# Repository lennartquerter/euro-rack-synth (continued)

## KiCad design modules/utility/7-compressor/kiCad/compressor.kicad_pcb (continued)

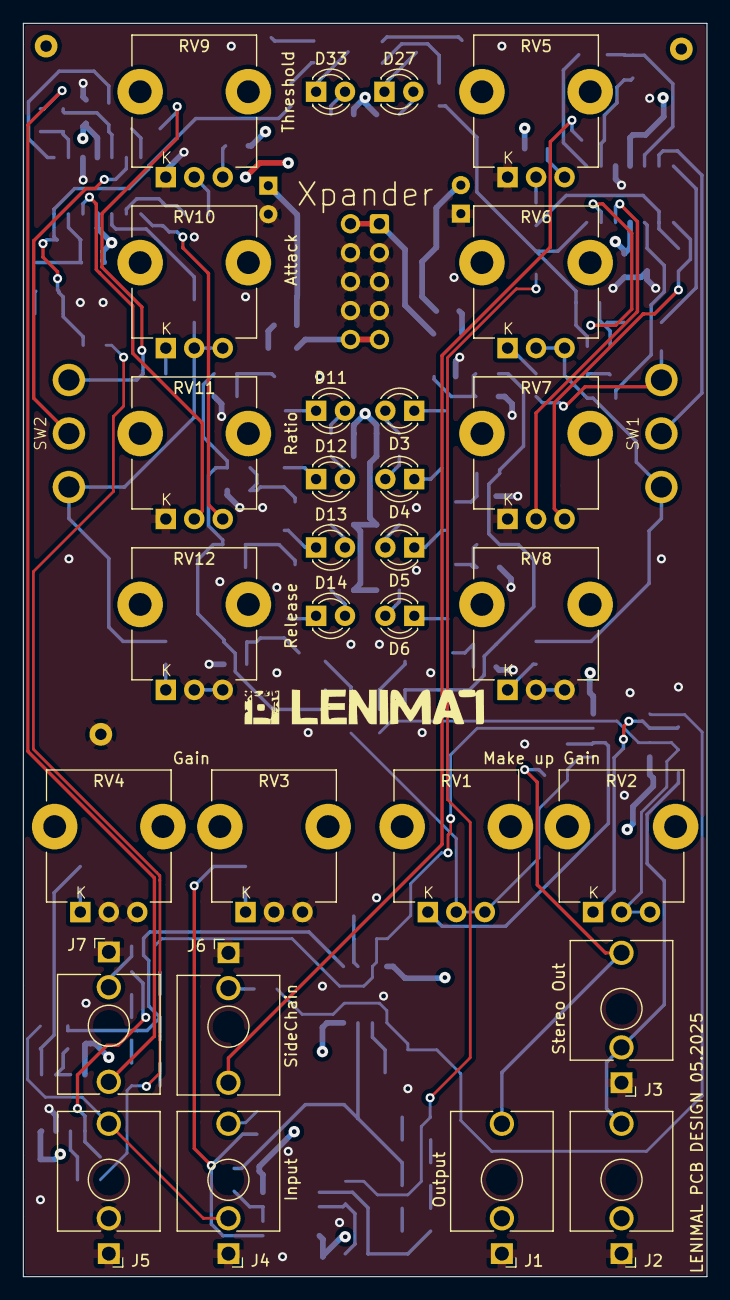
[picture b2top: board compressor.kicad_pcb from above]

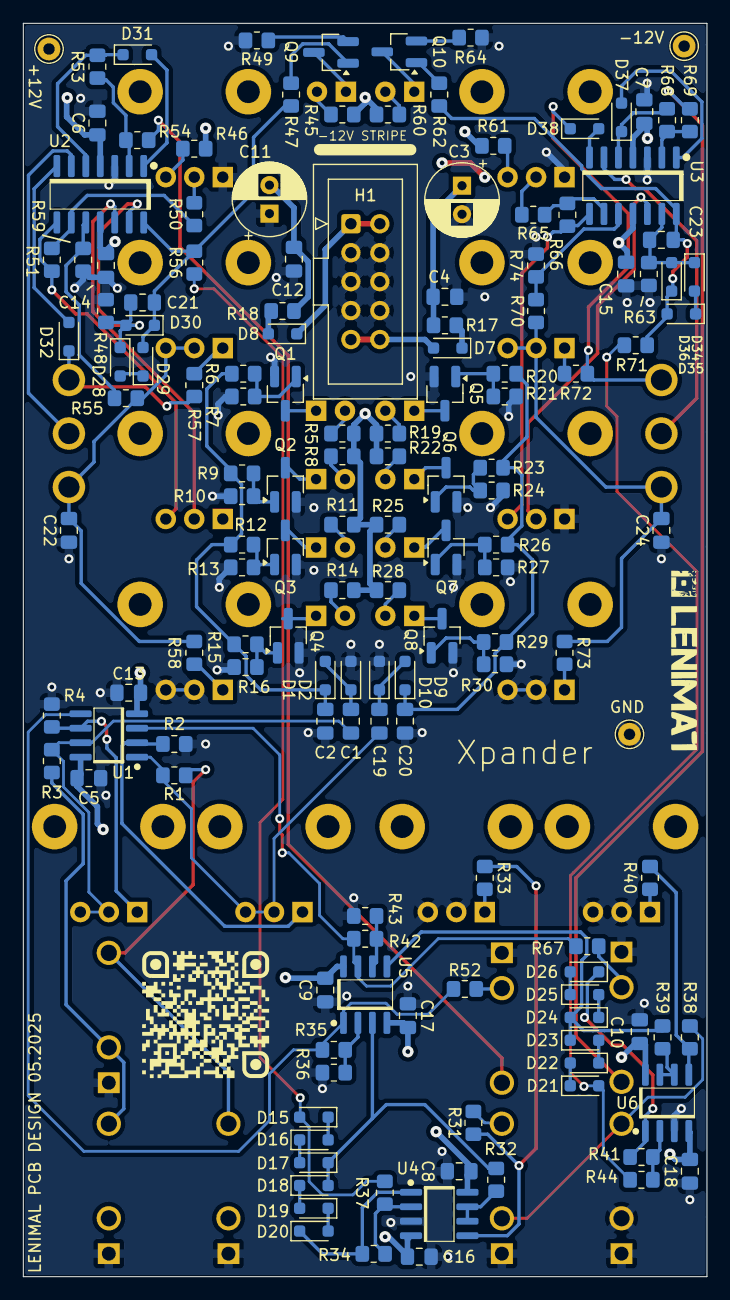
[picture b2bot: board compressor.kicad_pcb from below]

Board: 4 copper layers, 60.0 x 110.0 mm, 177 parts (146 on the bottom side), 117 nets.

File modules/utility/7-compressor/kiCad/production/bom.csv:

Designator,Footprint,Quantity,Value,LCSC Part #
"C1, C19, C2, C20, C22, C24",0805,6,1.5uF,
"C10, C12, C13, C14, C15, C16, C17, C18, C4, C5, C6, C7, C8, C9",0805,14,100nF,
"C11, C3",CP_Radial_D6.3mm_P2.50mm,2,47uF,
"C21, C23",0805,2,680pF,
"D1, D10, D15, D16, D17, D18, D19, D2, D20, D21, D22, D23, D24, D25, D26, D28, D29, D30, D31, D32, D34, D35, D36, D37, D38, D9",D_SOD-323_HandSoldering,26,1N4148WS,
"D11, D12, D13, D14, D27, D3, D33, D4, D5, D6",LED_D3.0mm,10,LED,
"D7, D8",D_SOD-323_HandSoldering,2,1N5819WS,
H1,IDC-Header_2x05_P2.54mm_Vertical,1,Conn_02x05_PWR_Eurorack,
J1,Jack_3.5mm_QingPu_WQP-PJ398SM_Vertical_CircularHoles,1,LEFT_OUT,
J2,Jack_3.5mm_QingPu_WQP-PJ398SM_Vertical_CircularHoles,1,RIGHT_OUT,
J3,Jack_3.5mm_QingPu_WQP-PJ398SM_Vertical_CircularHoles,1,STEREO_OUT,
"J4, J5",Jack_3.5mm_QingPu_WQP-PJ398SM_Vertical_CircularHoles,2,INPUT,
"J6, J7",Jack_3.5mm_QingPu_WQP-PJ398SM_Vertical_CircularHoles,2,SIDECHAIN_IN,
"Q1, Q10, Q2, Q3, Q4, Q5, Q6, Q7, Q8, Q9",SOT-23_Handsoldering,10,MMBT3904,
"R1, R3, R52, R67",0805,4,1K,
"R10, R13, R16, R21, R24, R27, R30, R7",0805,8,33K,
"R11, R14, R19, R22, R25, R28, R5, R8",0805,8,3K3,
"R12, R26",0805,2,220K,
"R15, R29",0805,2,330K,
"R17, R18",0805,2,10R,
"R2, R4",0805,2,20K,
"R20, R6",0805,2,47K,
"R23, R9",0805,2,120K,
"R31, R32, R34, R35, R37, R38, R39, R41, R42, R44, R48, R50, R51, R53, R54, R58, R63, R65, R66, R68, R69, R73",0805,22,100K,
"R33, R36, R40, R43, R46, R47, R61, R62",0805,8,10K,
"R45, R60",0805,2,470R,
"R49, R64",0805,2,0R,
"R55, R59, R70, R74",0805,4,470K,
"R56, R71",0805,2,2K,
"R57, R72",0805,2,200R,
"RV1, RV11, RV2, RV7",Potentiometer_TT_P0915N,4,A100K,
"RV10, RV6",Potentiometer_TT_P0915N,2,A500K,
"RV12, RV8",Potentiometer_TT_P0915N,2,A1M,
"RV3, RV4",Potentiometer_TT_P0915N,2,A20K,
"RV5, RV9",Potentiometer_TT_P0915N,2,A10K,
"SW1, SW2",SW_default,2,SW_SPDT,
"U1, U4, U5, U6",SOIC-8,4,TL072,
"U2, U3",SOIC-14,2,TL074,

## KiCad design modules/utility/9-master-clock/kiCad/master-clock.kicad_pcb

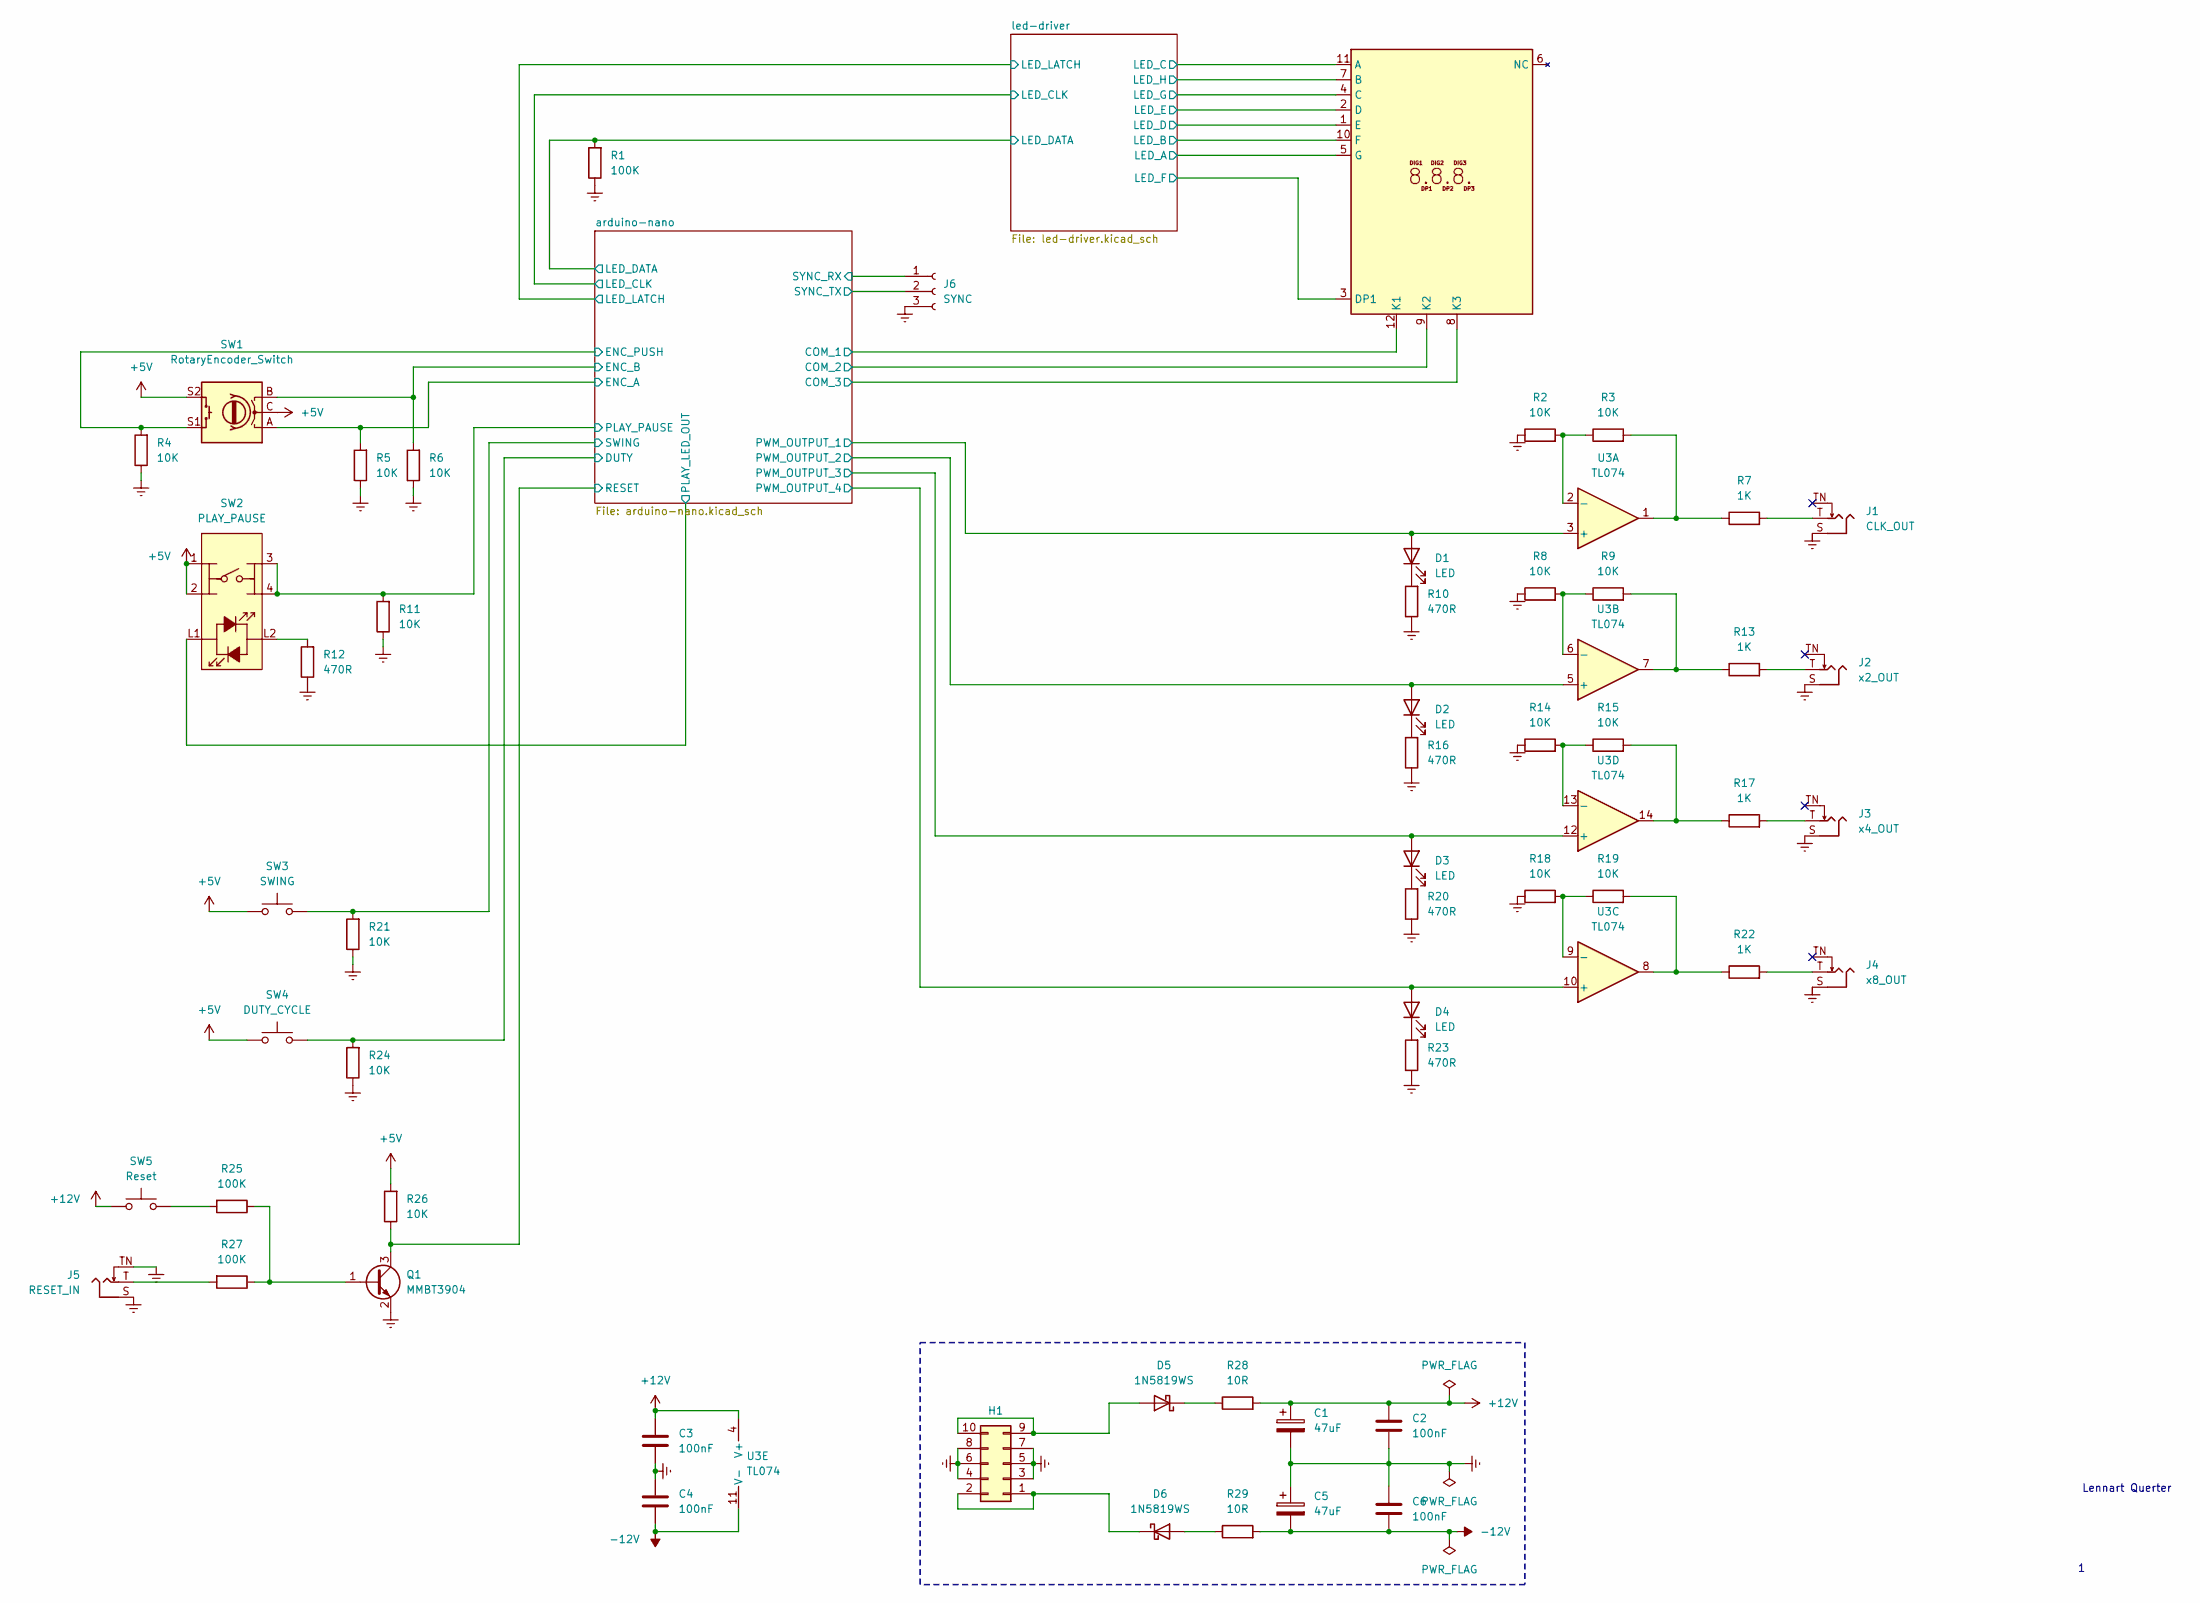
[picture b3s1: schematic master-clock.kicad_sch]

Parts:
C1, C5: 47uF; CP_Radial_D5.0mm_P2.50mm
C2, C3, C4, C6: 100nF; C_0805_2012Metric_Pad1.18x1.45mm_HandSolder
D1, D2, D3, D4: LED; LED_D3.0mm
D5, D6: 1N5819WS; D_SOD-323_HandSoldering
H1: Conn_02x05_PWR_Eurorack; PinSocket_2x05_P2.54mm_Vertical
J1: CLK_OUT; Jack_3.5mm_QingPu_WQP-PJ398SM_Vertical_CircularHoles
J2: x2_OUT; Jack_3.5mm_QingPu_WQP-PJ398SM_Vertical_CircularHoles
J3: x4_OUT; Jack_3.5mm_QingPu_WQP-PJ398SM_Vertical_CircularHoles
J4: x8_OUT; Jack_3.5mm_QingPu_WQP-PJ398SM_Vertical_CircularHoles
J5: RESET_IN; Jack_3.5mm_QingPu_WQP-PJ398SM_Vertical_CircularHoles
J6: SYNC; PinSocket_1x03_P2.54mm_Vertical
Q1: MMBT3904; SOT-23_Handsoldering
R1, R25, R27: 100K; R_0805_2012Metric_Pad1.20x1.40mm_HandSolder
R2, R3, R4, R5, R6, R8, R9, R11, R14, R15, R18, R19, R21, R24, R26: 10K; R_0805_2012Metric_Pad1.20x1.40mm_HandSolder
R7, R13, R17, R22: 1K; R_0805_2012Metric_Pad1.20x1.40mm_HandSolder
R10, R12, R16, R20, R23: 470R; R_0805_2012Metric_Pad1.20x1.40mm_HandSolder
R28, R29: 10R; R_0805_2012Metric_Pad1.20x1.40mm_HandSolder
SW1: RotaryEncoder_Switch; RotaryEncoder_Alps_EC11E-Switch_Vertical_H20mm_CircularMoun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
SW2: PLAY_PAUSE; ML6-H2T2GQA
SW3: SWING; SW_PUSH_6mm
SW4: DUTY_CYCLE; SW_PUSH_6mm
SW5: Reset; SW_PUSH_6mm
U1: 3x7-segment_display; 3x7-segment-display_SP410361N
U3: TL074; SOIC-14

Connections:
+5V: R26.2, SW1.C, SW1.S2, SW2.1, SW2.2, SW3.1, SW4.1; also elsewhere on the board
+12V: C1.1, C2.1, C3.1, R28.2, SW5.1, U3.4 (V+); also elsewhere on the board
-12V: C4.2, C5.2, C6.2, R29.2, U3.11 (V-)
/arduino-nano/COM_1: U1.12 (K1); also elsewhere on the board
/arduino-nano/COM_2: U1.9 (K2); also elsewhere on the board
/arduino-nano/COM_3: U1.8 (K3); also elsewhere on the board
/arduino-nano/DUTY: R24.2, SW4.2; also elsewhere on the board
/arduino-nano/ENC_A: R5.2, SW1.A; also elsewhere on the board
/arduino-nano/ENC_B: R6.2, SW1.B; also elsewhere on the board
/arduino-nano/ENC_PUSH: R4.2, SW1.S1; also elsewhere on the board
/arduino-nano/LED_DATA: R1.2; also elsewhere on the board
/arduino-nano/PLAY_LED_OUT: SW2.L1; also elsewhere on the board
/arduino-nano/PLAY_PAUSE: R11.2, SW2.3, SW2.4 (A); also elsewhere on the board
/arduino-nano/PWM_OUTPUT_1: D1.2 (A), U3.3 (+); also elsewhere on the board
/arduino-nano/PWM_OUTPUT_2: D2.2 (A), U3.5 (+); also elsewhere on the board
/arduino-nano/PWM_OUTPUT_3: D3.2 (A), U3.12 (+); also elsewhere on the board
/arduino-nano/PWM_OUTPUT_4: D4.2 (A), U3.10 (+); also elsewhere on the board
/arduino-nano/RESET: Q1.3 (C), R26.1; also elsewhere on the board
/arduino-nano/SWING: R21.2, SW3.2; also elsewhere on the board
/arduino-nano/SYNC_RX: J6.1; also elsewhere on the board
/arduino-nano/SYNC_TX: J6.2; also elsewhere on the board
/led-driver/LED_A: U1.5 (G); also elsewhere on the board
/led-driver/LED_B: U1.10 (F); also elsewhere on the board
/led-driver/LED_C: U1.11 (A); also elsewhere on the board
/led-driver/LED_D: U1.1 (E); also elsewhere on the board
/led-driver/LED_E: U1.2 (D); also elsewhere on the board
/led-driver/LED_F: U1.3 (DP1); also elsewhere on the board
/led-driver/LED_G: U1.4 (C); also elsewhere on the board
/led-driver/LED_H: U1.7 (B); also elsewhere on the board
GNDREF: C1.2, C2.2, C3.2, C4.1, C5.1, C6.1, H1.3, H1.4, H1.5, H1.6, H1.7, H1.8, J1.S, J2.S, J3.S, J4.S, J5.S, J5.TN, J6.3, Q1.2 (E), R1.1, R2.1, R4.1, R5.1, R6.1, R8.1, R10.1, R11.1, R12.1, R14.1, R16.1, R18.1, R20.1, R21.1, R23.1, R24.1; also elsewhere on the board
unnamed: D1.1 (K), R10.2
unnamed: D2.1 (K), R16.2
unnamed: D3.1 (K), R20.2
unnamed: D4.1 (K), R23.2
unnamed: D5.2 (A), H1.9, H1.10
unnamed: D5.1 (K), R28.1
unnamed: D6.2 (A), R29.1
unnamed: D6.1 (K), H1.1, H1.2
unnamed: J1.T, R7.2
unnamed: J2.T, R13.2
unnamed: J3.T, R17.2
unnamed: J4.T, R22.2
unnamed: J5.T, R27.2
unnamed: Q1.1 (B), R25.1, R27.1
unnamed: R3.2, R7.1, U3.1
unnamed: R12.2, SW2.L2
unnamed: R9.2, R13.1, U3.7
unnamed: R15.2, R17.1, U3.14
unnamed: R19.2, R22.1, U3.8
unnamed: R25.2, SW5.2
unnamed: R2.2, R3.1, U3.2 (-)
unnamed: R8.2, R9.1, U3.6 (-)
unnamed: R18.2, R19.1, U3.9 (-)
unnamed: R14.2, R15.1, U3.13 (-)

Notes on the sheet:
Lennart Querter

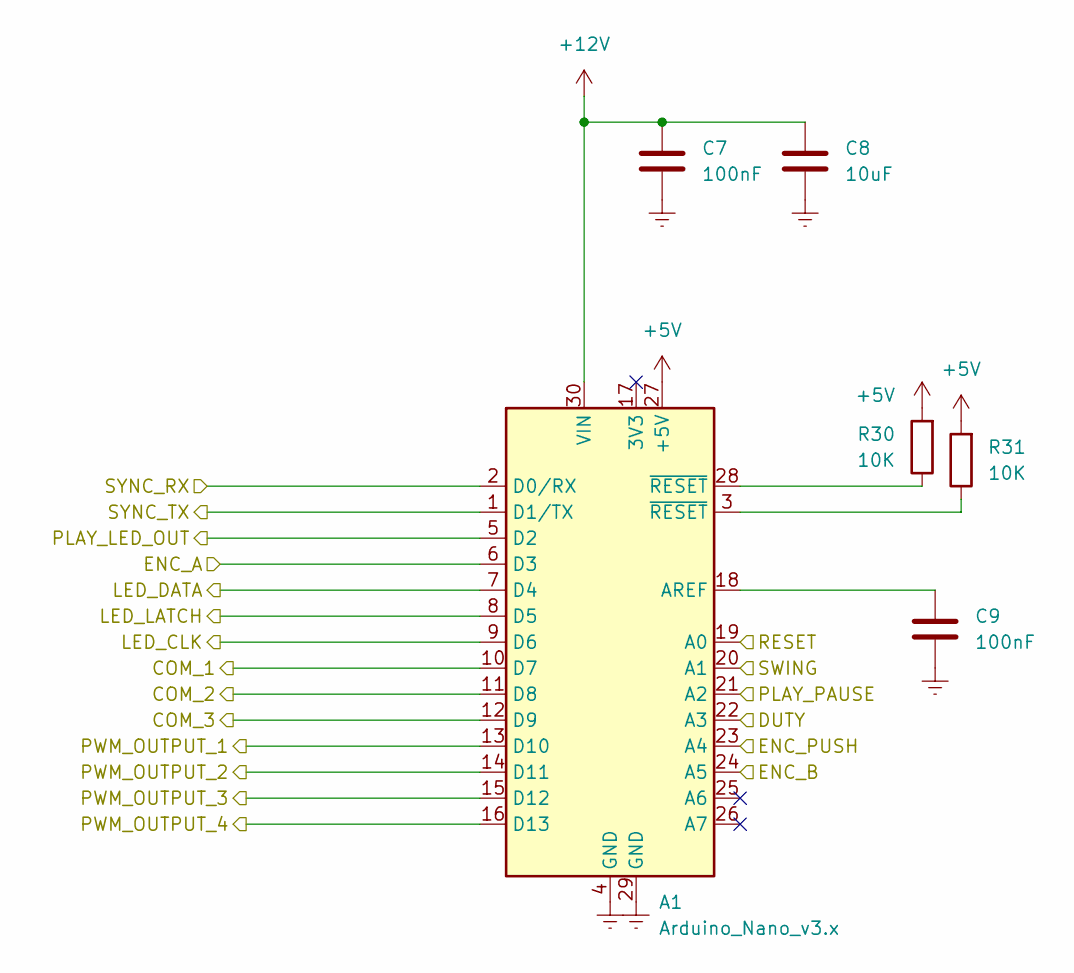
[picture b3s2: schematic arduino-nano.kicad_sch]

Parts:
A1: Arduino_Nano_v3.x; Arduino_Nano_MOD
C7, C9: 100nF; C_0805_2012Metric_Pad1.18x1.45mm_HandSolder
C8: 10uF; C_0805_2012Metric_Pad1.18x1.45mm_HandSolder
R30, R31: 10K; R_0805_2012Metric_Pad1.20x1.40mm_HandSolder

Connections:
+5V: A1.27 (+5V), R30.2, R31.2; also elsewhere on the board
+12V: A1.30 (VIN), C7.1, C8.1; also elsewhere on the board
/arduino-nano/COM_1: A1.10 (D7); also elsewhere on the board
/arduino-nano/COM_2: A1.11 (D8); also elsewhere on the board
/arduino-nano/COM_3: A1.12 (D9); also elsewhere on the board
/arduino-nano/DUTY: A1.22 (A3); also elsewhere on the board
/arduino-nano/ENC_A: A1.6 (D3); also elsewhere on the board
/arduino-nano/ENC_B: A1.24 (A5); also elsewhere on the board
/arduino-nano/ENC_PUSH: A1.23 (A4); also elsewhere on the board
/arduino-nano/LED_CLK: A1.9 (D6); also elsewhere on the board
/arduino-nano/LED_DATA: A1.7 (D4); also elsewhere on the board
/arduino-nano/LED_LATCH: A1.8 (D5); also elsewhere on the board
/arduino-nano/PLAY_LED_OUT: A1.5 (D2); also elsewhere on the board
/arduino-nano/PLAY_PAUSE: A1.21 (A2); also elsewhere on the board
/arduino-nano/PWM_OUTPUT_1: A1.13 (D10); also elsewhere on the board
/arduino-nano/PWM_OUTPUT_2: A1.14 (D11); also elsewhere on the board
/arduino-nano/PWM_OUTPUT_3: A1.15 (D12); also elsewhere on the board
/arduino-nano/PWM_OUTPUT_4: A1.16 (D13); also elsewhere on the board
/arduino-nano/RESET: A1.19 (A0); also elsewhere on the board
/arduino-nano/SWING: A1.20 (A1); also elsewhere on the board
/arduino-nano/SYNC_RX: A1.2 (D0/RX); also elsewhere on the board
/arduino-nano/SYNC_TX: A1.1 (D1/TX); also elsewhere on the board
GNDREF: A1.4 (GND), A1.29 (GND), C7.2, C8.2, C9.2; also elsewhere on the board
unnamed: A1.18 (AREF), C9.1
unnamed: A1.3 (~RESET), R31.1
unnamed: A1.28 (~RESET), R30.1

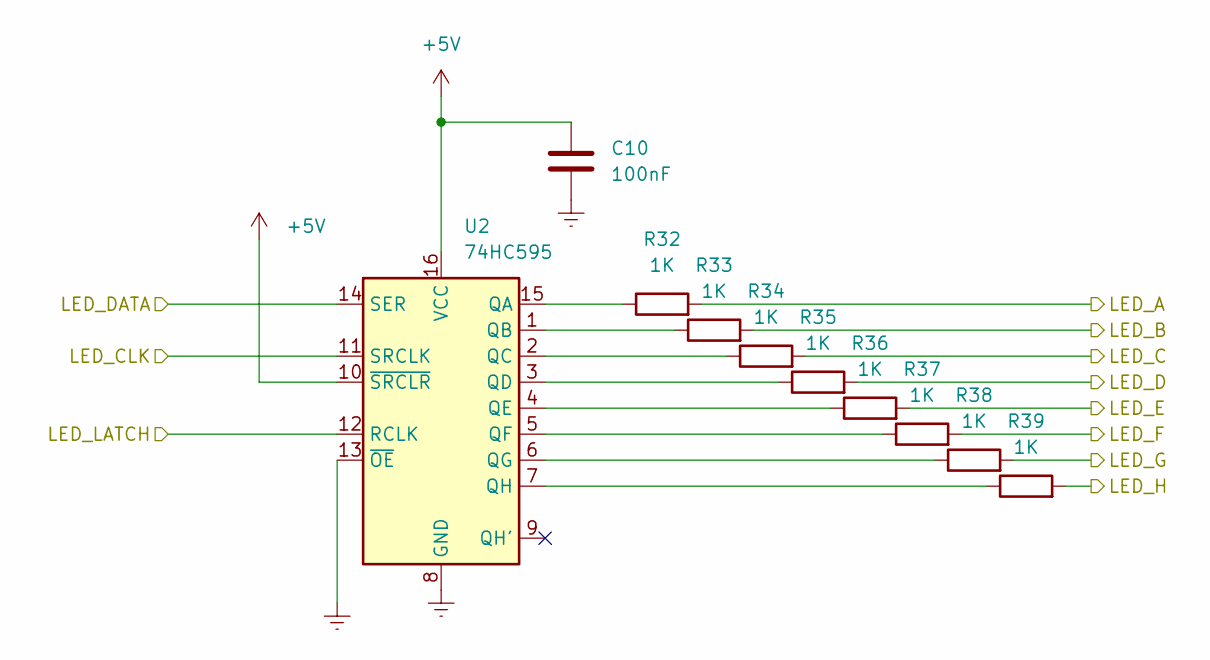
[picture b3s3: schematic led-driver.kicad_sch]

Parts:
C10: 100nF; C_0805_2012Metric_Pad1.18x1.45mm_HandSolder
R32, R33, R34, R35, R36, R37, R38, R39: 1K; R_0805_2012Metric_Pad1.20x1.40mm_HandSolder
U2: 74HC595; SOIC-16

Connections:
+5V: C10.1, U2.10 (~SRCLR), U2.16 (VCC); also elsewhere on the board
/arduino-nano/LED_CLK: U2.11 (SRCLK); also elsewhere on the board
/arduino-nano/LED_DATA: U2.14 (SER); also elsewhere on the board
/arduino-nano/LED_LATCH: U2.12 (RCLK); also elsewhere on the board
/led-driver/LED_A: R32.2; also elsewhere on the board
/led-driver/LED_B: R33.2; also elsewhere on the board
/led-driver/LED_C: R34.2; also elsewhere on the board
/led-driver/LED_D: R35.2; also elsewhere on the board
/led-driver/LED_E: R36.2; also elsewhere on the board
/led-driver/LED_F: R37.2; also elsewhere on the board
/led-driver/LED_G: R38.2; also elsewhere on the board
/led-driver/LED_H: R39.2; also elsewhere on the board
GNDREF: C10.2, U2.8 (GND), U2.13 (~OE); also elsewhere on the board
unnamed: R32.1, U2.15 (QA)
unnamed: R33.1, U2.1 (QB)
unnamed: R34.1, U2.2 (QC)
unnamed: R35.1, U2.3 (QD)
unnamed: R36.1, U2.4 (QE)
unnamed: R37.1, U2.5 (QF)
unnamed: R38.1, U2.6 (QG)
unnamed: R39.1, U2.7 (QH)

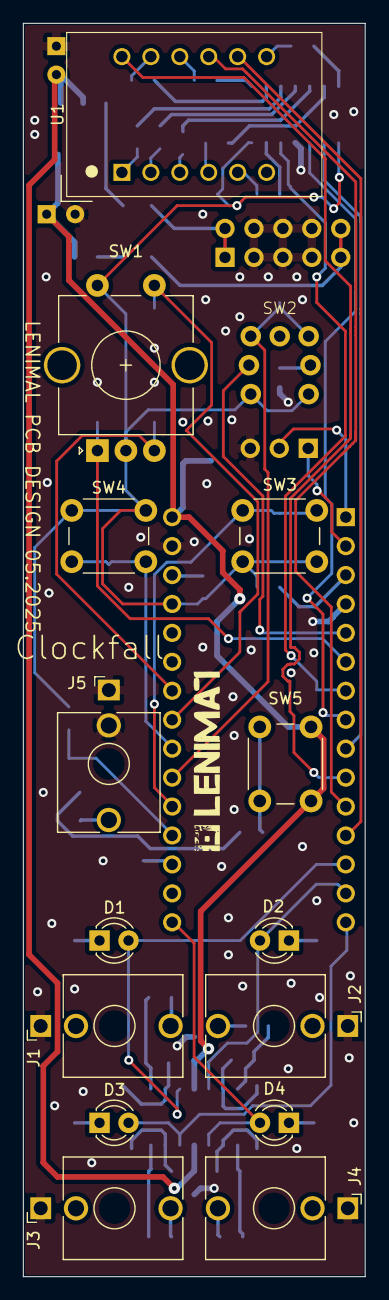
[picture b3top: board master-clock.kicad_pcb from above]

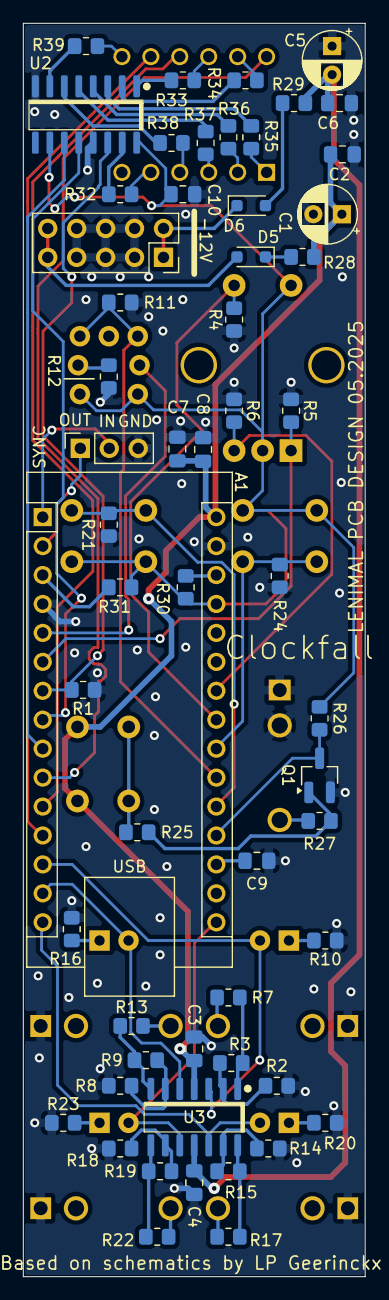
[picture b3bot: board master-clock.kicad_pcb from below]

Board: 2 copper layers, 30.0 x 110.0 mm, 72 parts (57 on the bottom side), 67 nets.

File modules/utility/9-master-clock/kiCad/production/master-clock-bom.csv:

Designator,Footprint,Quantity,Value,LCSC Part #
A1,Arduino_Nano_MOD,1,Arduino_Nano_v3.x,
"C1, C5",CP_Radial_D5.0mm_P2.50mm,2,47uF,
"C10, C2, C3, C4, C6, C7, C9",0805,7,100nF,
C8,0805,1,10uF,
"D1, D2, D3, D4",LED_D3.0mm,4,LED,
"D5, D6",D_SOD-323_HandSoldering,2,1N5819WS,
H1,PinSocket_2x05_P2.54mm_Vertical,1,Conn_02x05_PWR_Eurorack,
J1,Jack_3.5mm_QingPu_WQP-PJ398SM_Vertical_CircularHoles,1,CLK_OUT,
J2,Jack_3.5mm_QingPu_WQP-PJ398SM_Vertical_CircularHoles,1,x2_OUT,
J3,Jack_3.5mm_QingPu_WQP-PJ398SM_Vertical_CircularHoles,1,x4_OUT,
J4,Jack_3.5mm_QingPu_WQP-PJ398SM_Vertical_CircularHoles,1,x8_OUT,
J5,Jack_3.5mm_QingPu_WQP-PJ398SM_Vertical_CircularHoles,1,RESET_IN,
J6,PinSocket_1x03_P2.54mm_Vertical,1,SYNC,
Q1,SOT-23_Handsoldering,1,MMBT3904,
"R1, R25, R27",0805,3,100K,
"R10, R12, R16, R20, R23",0805,5,470R,
"R11, R14, R15, R18, R19, R2, R21, R24, R26, R3, R30, R31, R4, R5, R6, R8, R9",0805,17,10K,
"R13, R17, R22, R32, R33, R34, R35, R36, R37, R38, R39, R7",0805,12,1K,
"R28, R29",0805,2,10R,
SW1,RotaryEncoder_Alps_EC11E-Switch_Vertical_H20mm_CircularMountingHoles,1,RotaryEncoder_Switch,
SW2,ML6-H2T2GQA,1,PLAY_PAUSE,
SW3,SW_PUSH_6mm,1,SWING,
SW4,SW_PUSH_6mm,1,DUTY_CYCLE,
SW5,SW_PUSH_6mm,1,Reset,
U1,3x7-segment-display_SP410361N,1,3x7-segment_display,
U2,SOIC-16,1,74HC595,
U3,SOIC-14,1,TL074,

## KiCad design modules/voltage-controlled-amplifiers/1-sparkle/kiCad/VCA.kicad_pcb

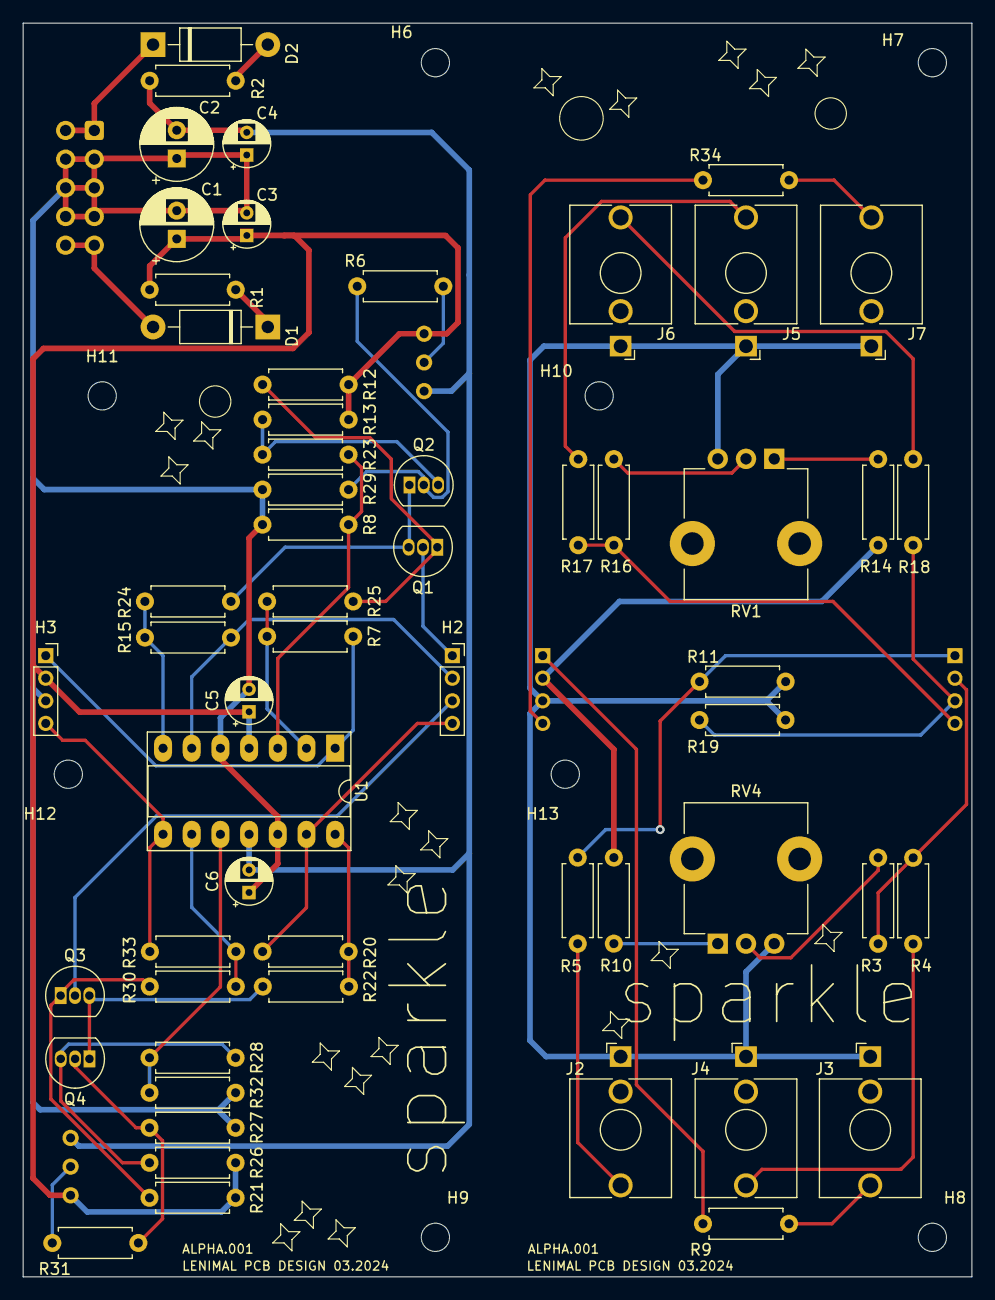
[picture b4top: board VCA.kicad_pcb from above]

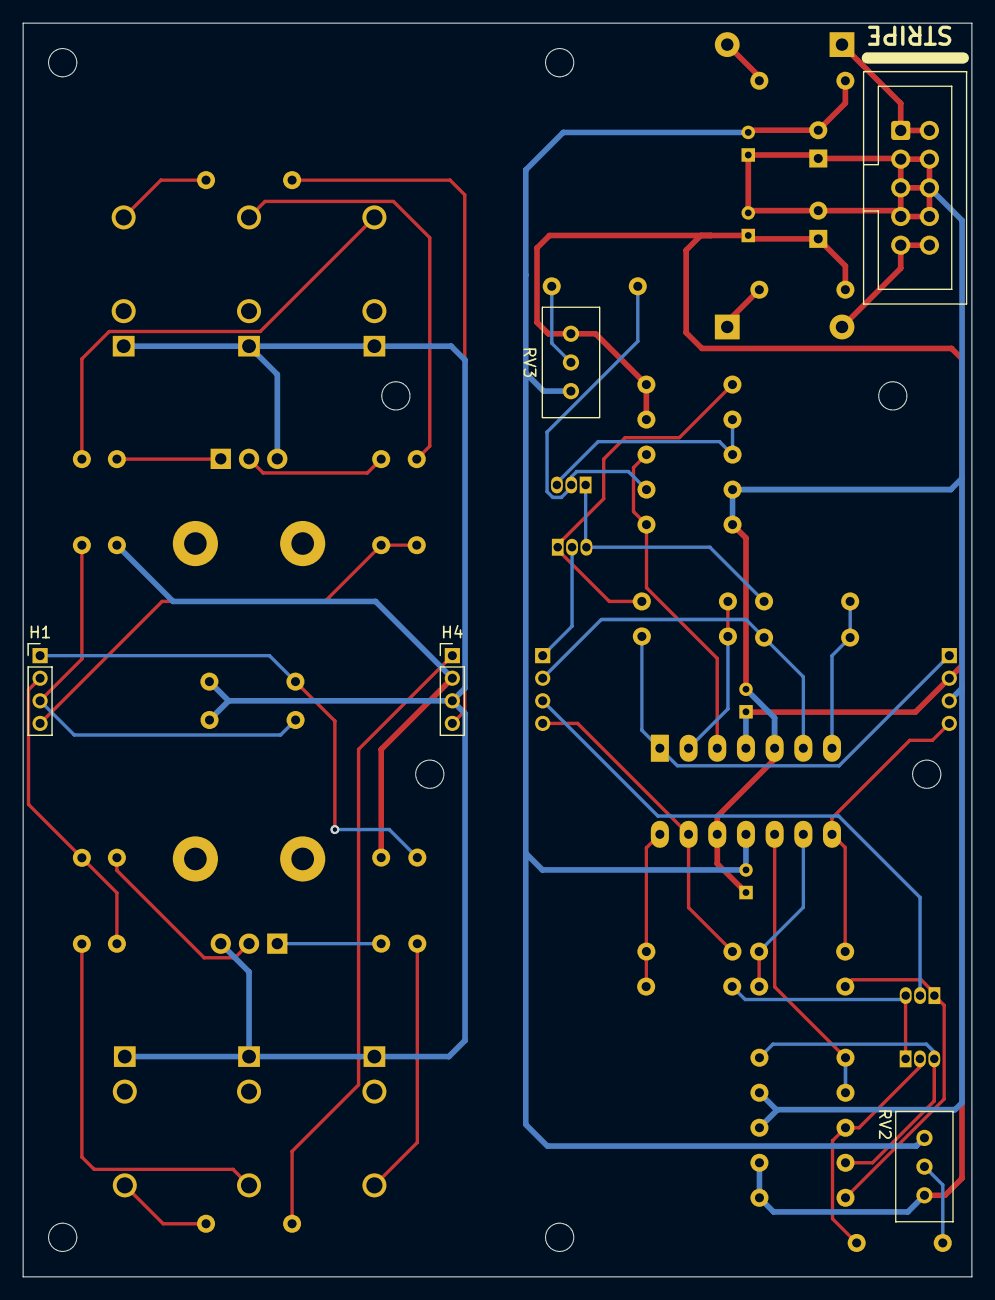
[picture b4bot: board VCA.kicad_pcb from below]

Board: 2 copper layers, 84.0 x 111.0 mm, 70 parts (5 on the bottom side), 45 nets.

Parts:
C1, C2: 47uF; CP_Radial_D6.3mm_P2.50mm
C3, C4, C5, C6: 0.1uF; CP_Radial_D4.0mm_P2.00mm
D1, D2: 1N5819; D_DO-41_SOD81_P10.16mm_Horizontal
H1, H4: TOP_4_SGL; PinHeader_1x04_P2.00mm_Vertical
H2, H3: BTM_4_SGL; PinSocket_1x04_P2.00mm_Vertical
H5: Conn_02x05_PWR_Eurorack; CONN_02x05_PWR
H6, H7, H8, H9, H10, H11, H12, H13: MountingHole; MountingHole_2.5mm
J2, J6: IN_1; Jack_3.5mm_QingPu_WQP-PJ398SM_Vertical_CircularHoles
J3, J7: OUT_1; Jack_3.5mm_QingPu_WQP-PJ398SM_Vertical_CircularHoles
J4, J5: CV_1; Jack_3.5mm_QingPu_WQP-PJ398SM_Vertical_CircularHoles
Q1, Q2, Q3, Q4: BC548; TO-92_Inline
R1, R2: 10; R_Axial_DIN0207_L6.3mm_D2.5mm_P7.62mm_Horizontal
R3, R4, R5, R6, R7, R8, R16, R17, R18, R31, R32, R33: 100K; R_Axial_DIN0207_L6.3mm_D2.5mm_P7.62mm_Horizontal
R9, R34: 1K; R_Axial_DIN0207_L6.3mm_D2.5mm_P7.62mm_Horizontal
R10, R12, R13, R14, R21, R26: 20K; R_Axial_DIN0207_L6.3mm_D2.5mm_P7.62mm_Horizontal
R11, R19, R27, R29: 100; R_Axial_DIN0207_L6.3mm_D2.5mm_P7.62mm_Horizontal
R15, R20: 82K; R_Axial_DIN0207_L6.3mm_D2.5mm_P7.62mm_Horizontal
R22, R23, R24, R25, R28, R30: 10K; R_Axial_DIN0207_L6.3mm_D2.5mm_P7.62mm_Horizontal
RV1, RV4: 100K; Potentiometer_TT_P0915N
RV2, RV3: 100K; Potentiometer_Bourns_3296W_Vertical
U1: TL074; DIP-14_W7.62mm_Socket_LongPads

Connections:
+12V: C1.1, C3.1, C5.1, H3.2, H4.2, R1.2, R10.2, R12.2, R13.2, R14.2, R21.2, R26.2, RV2.1, RV3.1, U1.4 (V+)
-12V: C2.2, C4.2, C6.2, R2.2, RV2.3, RV3.3, U1.11 (V-)
GNDREF: C1.2, C2.1, C3.2, C4.1, C5.2, C6.1, H3.3, H4.3, H5.3, H5.4, H5.5, H5.6, H5.7, H5.8, J2.S, J3.S, J4.S, J5.S, J6.S, J7.S, R8.1, R11.1, R19.1, R27.1, R29.1, R32.1, RV1.3, RV4.3, U1.5 (+), U1.12 (+)
unnamed: D1.2 (A), H5.9, H5.10
unnamed: D1.1 (K), R1.1
unnamed: D2.2 (A), R2.1
unnamed: D2.1 (K), H5.1, H5.2
unnamed: H1.1, R5.2, R11.2
unnamed: H1.2, R3.2, R4.2
unnamed: H1.3, R18.2, R19.2
unnamed: H1.4, R16.2, R17.2
unnamed: H3.1, R7.1, U1.1
unnamed: H3.4, R33.1, U1.8
unnamed: H4.1, R9.1
unnamed: H4.4, R34.1
unnamed: J2.T, R5.1
unnamed: J3.T, R9.2
unnamed: J4.T, R4.1
unnamed: J5.T, R17.1
unnamed: J6.T, R18.1
unnamed: J7.T, R34.2
unnamed: H2.1, Q1.2 (B)
unnamed: Q1.1 (C), R12.1, R25.1
unnamed: Q1.3 (E), Q2.1 (C), R24.2
unnamed: Q2.2 (B), R6.1, R29.2
unnamed: Q2.3 (E), R13.1, R23.1
unnamed: H2.3, Q3.2 (B)
unnamed: Q3.1 (C), R21.1, R30.1
unnamed: Q3.3 (E), Q4.1 (C), R22.2
unnamed: Q4.2 (B), R27.2, R31.1
unnamed: Q4.3 (E), R26.1, R28.1
unnamed: R3.1, RV4.2
unnamed: R6.2, RV3.2
unnamed: R10.1, RV4.1
unnamed: R14.1, RV1.1
unnamed: R15.2, R24.1, U1.7
unnamed: R16.1, RV1.2
unnamed: R20.2, R22.1, U1.14
unnamed: R31.2, RV2.2
unnamed: R8.2, R23.2, U1.3 (+)
unnamed: R7.2, R25.2, U1.2 (-)
unnamed: H2.2, R15.1, U1.6 (-)
unnamed: R28.2, R32.2, U1.10 (+)
unnamed: R30.2, R33.2, U1.9 (-)
unnamed: H2.4, R20.1, U1.13 (-)
